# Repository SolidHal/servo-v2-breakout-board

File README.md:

Servo V2 breakout board
offset and spacing designed for compatability with gru-kevin, but likely can be made to work with other chromebooks

check out the images folder for what it looks like fabbed

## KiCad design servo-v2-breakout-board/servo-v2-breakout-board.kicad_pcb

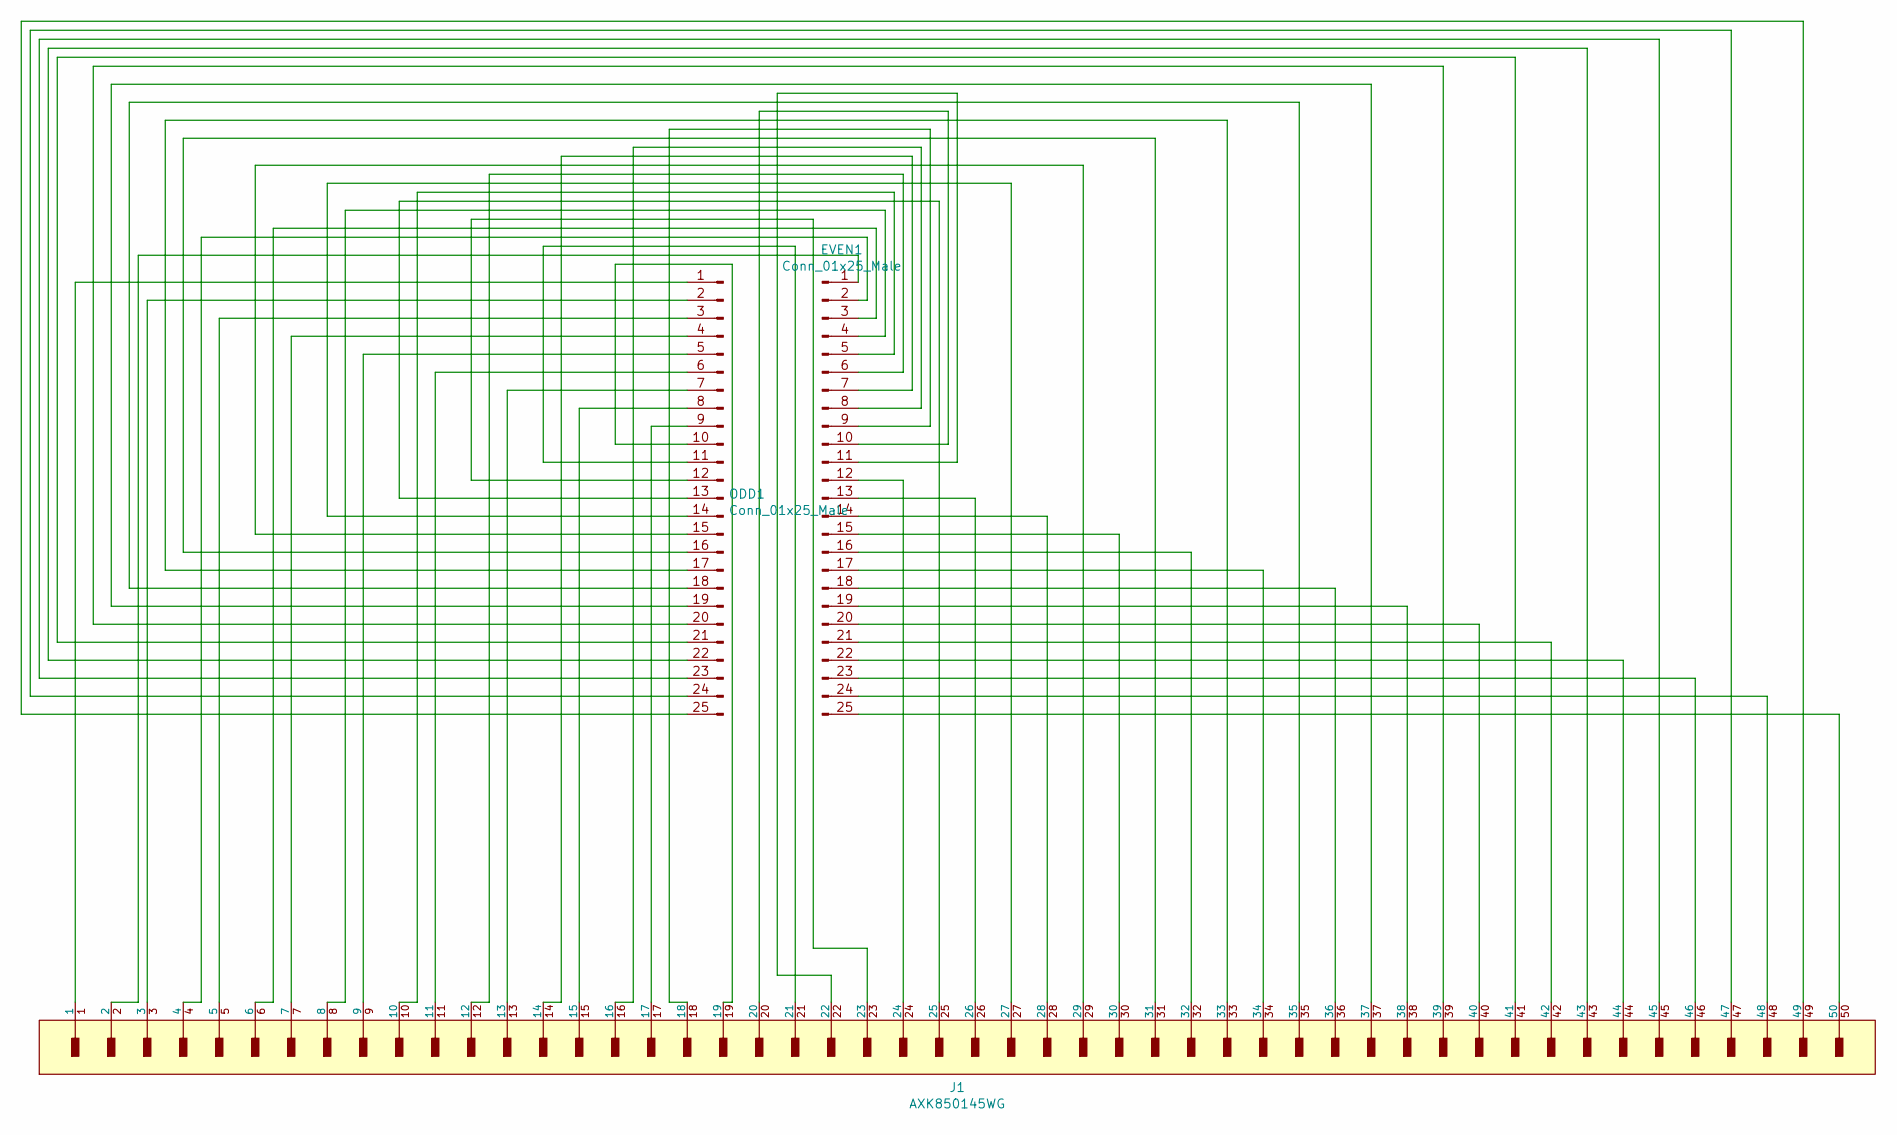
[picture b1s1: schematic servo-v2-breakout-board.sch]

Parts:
EVEN1: Conn_01x25_Male; PinHeader_1x25_P2.54mm_Vertical
J1: AXK850145WG; Panasonic_Corporation-AXK850145WG-0; mouser part number 769-AXK850145WG; digikey description 50 Position Connector Header, Outer Shr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
ODD1: Conn_01x25_Male; PinHeader_1x25_P2.54mm_Vertical

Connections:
unnamed: EVEN1.1, J1.2
unnamed: EVEN1.2, J1.4
unnamed: EVEN1.3, J1.6
unnamed: EVEN1.4, J1.8
unnamed: EVEN1.5, J1.10
unnamed: EVEN1.6, J1.12
unnamed: EVEN1.7, J1.14
unnamed: EVEN1.8, J1.16
unnamed: EVEN1.9, J1.18
unnamed: EVEN1.10, J1.20
unnamed: EVEN1.11, J1.22
unnamed: EVEN1.12, J1.24
unnamed: EVEN1.13, J1.26
unnamed: EVEN1.14, J1.28
unnamed: EVEN1.15, J1.30
unnamed: EVEN1.16, J1.32
unnamed: EVEN1.17, J1.34
unnamed: EVEN1.18, J1.36
unnamed: EVEN1.19, J1.38
unnamed: EVEN1.20, J1.40
unnamed: EVEN1.21, J1.42
unnamed: EVEN1.22, J1.44
unnamed: EVEN1.23, J1.46
unnamed: EVEN1.24, J1.48
unnamed: EVEN1.25, J1.50
unnamed: J1.1, ODD1.1
unnamed: J1.3, ODD1.2
unnamed: J1.5, ODD1.3
unnamed: J1.7, ODD1.4
unnamed: J1.9, ODD1.5
unnamed: J1.11, ODD1.6
unnamed: J1.13, ODD1.7
unnamed: J1.15, ODD1.8
unnamed: J1.17, ODD1.9
unnamed: J1.19, ODD1.10
unnamed: J1.21, ODD1.11
unnamed: J1.23, ODD1.12
unnamed: J1.25, ODD1.13
unnamed: J1.27, ODD1.14
unnamed: J1.29, ODD1.15
unnamed: J1.31, ODD1.16
unnamed: J1.33, ODD1.17
unnamed: J1.35, ODD1.18
unnamed: J1.37, ODD1.19
unnamed: J1.39, ODD1.20
unnamed: J1.41, ODD1.21
unnamed: J1.43, ODD1.22
unnamed: J1.45, ODD1.23
unnamed: J1.47, ODD1.24
unnamed: J1.49, ODD1.25

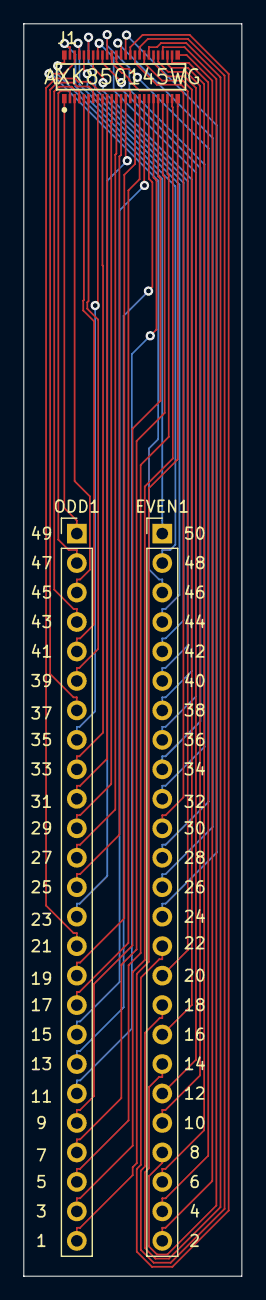
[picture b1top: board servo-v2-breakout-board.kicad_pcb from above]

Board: 2 copper layers, 18.8 x 108.0 mm, 3 parts (0 on the bottom side), 50 nets.

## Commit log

2020-11-08 commit work
2020-11-19 add some photos of version 1
2020-12-12 corrected pin numbering, which was mirrored on v1. changed headers to standard size
